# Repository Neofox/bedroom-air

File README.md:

# Bedroom Air

A bedroom CO₂ monitor you can build with an ESP32 and a Raspberry Pi Zero 2 W. Open Safari on your home Wi-Fi to see the room now, how high CO₂ climbed last night, and how much the temperature fell during a likely airing event.

## Build one

1. **Choose the parts.** Start with the 30-pin ESP32-WROOM-32, terminal-type Winsen MH-Z19C and DHT22 breakout. The BH1750 light sensor is optional. The parts list includes module variants, the Pi, power, and links to the carrier and case fasteners. [Parts list](docs/parts.md)
2. **Check the fit before ordering.** Print the A4 sheet at 100%, measure both 50 mm scale bars, and lay your actual modules on it. Then order the bare Rev A carrier and print the Rev C case. [Fit sheet](hardware/Board-fit-check.pdf) · [Gerbers and drills](hardware/Bedroom-Air-RevA-fabrication.zip) · [Printable parts](hardware/Case/)
3. **Solder and test.** Follow the connector map and staged power checks. The first USB flash can be done with the ESP32 lifted out of its sockets. [Carrier assembly](hardware/Assembly.md) · [Case assembly](hardware/Case/Assembly.md)
4. **Flash the ESP32 and enter your Wi-Fi settings over USB.** Once it joins your network, the live readings page is available at `http://bedroom-air.local/`. [Firmware setup and wireless updates](firmware/README.md)
5. **Set up the Pi for history and Apple Home.** The Pi saves one sample per minute on its microSD and serves the dashboard at `http://air-history.local:8080/`. After setup both devices can run on their own power supplies with the computer asleep. [Pi installation and pairing](pi/README.md)

The sensor and logging software ran on the breadboard prototype. The PCB and enclosure have electrical and digital fit checks. Physical fit and sensor behavior in a finished enclosure still need a first-build check.

## What you’ll see

**Live** refreshes roughly every three seconds. Select CO₂, temperature, humidity, or light to inspect its history. The ESP32 also keeps up to 24 hours of one-minute samples in RAM, which the Pi can collect after a Wi-Fi interruption while the ESP32 stays powered.

**Last night** shows the CO₂ peak, time above your chosen level, and how much of the night had valid data. **Airing out** looks for a sustained CO₂ drop and estimates the indoor temperature change and recovery time. Airing events are inferred from the sensors. The dashboard reports temperature change in °C. A heating bill would require energy-use and tariff data. [Example night report](docs/images/night-desktop.png) · [Phone dashboard](docs/images/live-phone.png)

**Apple Home** can show CO₂, temperature and humidity through the optional HomeKit service on the Pi. Light is available in the web dashboard. Each installation generates its own pairing code. The dashboard images in this repository use generated readings.

## Project files

| What you need | Where to find it |
| --- | --- |
| Arduino C++ sensor firmware, ESP32 web UI and bench sketches | [Firmware](firmware/) |
| Go logger, SQLite storage, Safari dashboard, reports and HomeKit service | [Pi source](pi/) |
| Ask Codex for current readings, recent trends, overnight CO₂ or inferred airing events | [Local MCP setup](mcp/) |
| PCB layout, schematic, local footprints and check reports | [Editable KiCad project](hardware/PCB/) · [Schematic PDF](hardware/PCB/Bedroom-Air-schematic.pdf) |
| Printable base, lid, sensor keeper, test gauge and parametric model | [Enclosure](hardware/Case/) |
| Design generation, rendering and fit checks | [Hardware design tools](hardware/tools/) |
| Prototype photos, wiring diagram and dashboard images | [Gallery](docs/gallery.md) |

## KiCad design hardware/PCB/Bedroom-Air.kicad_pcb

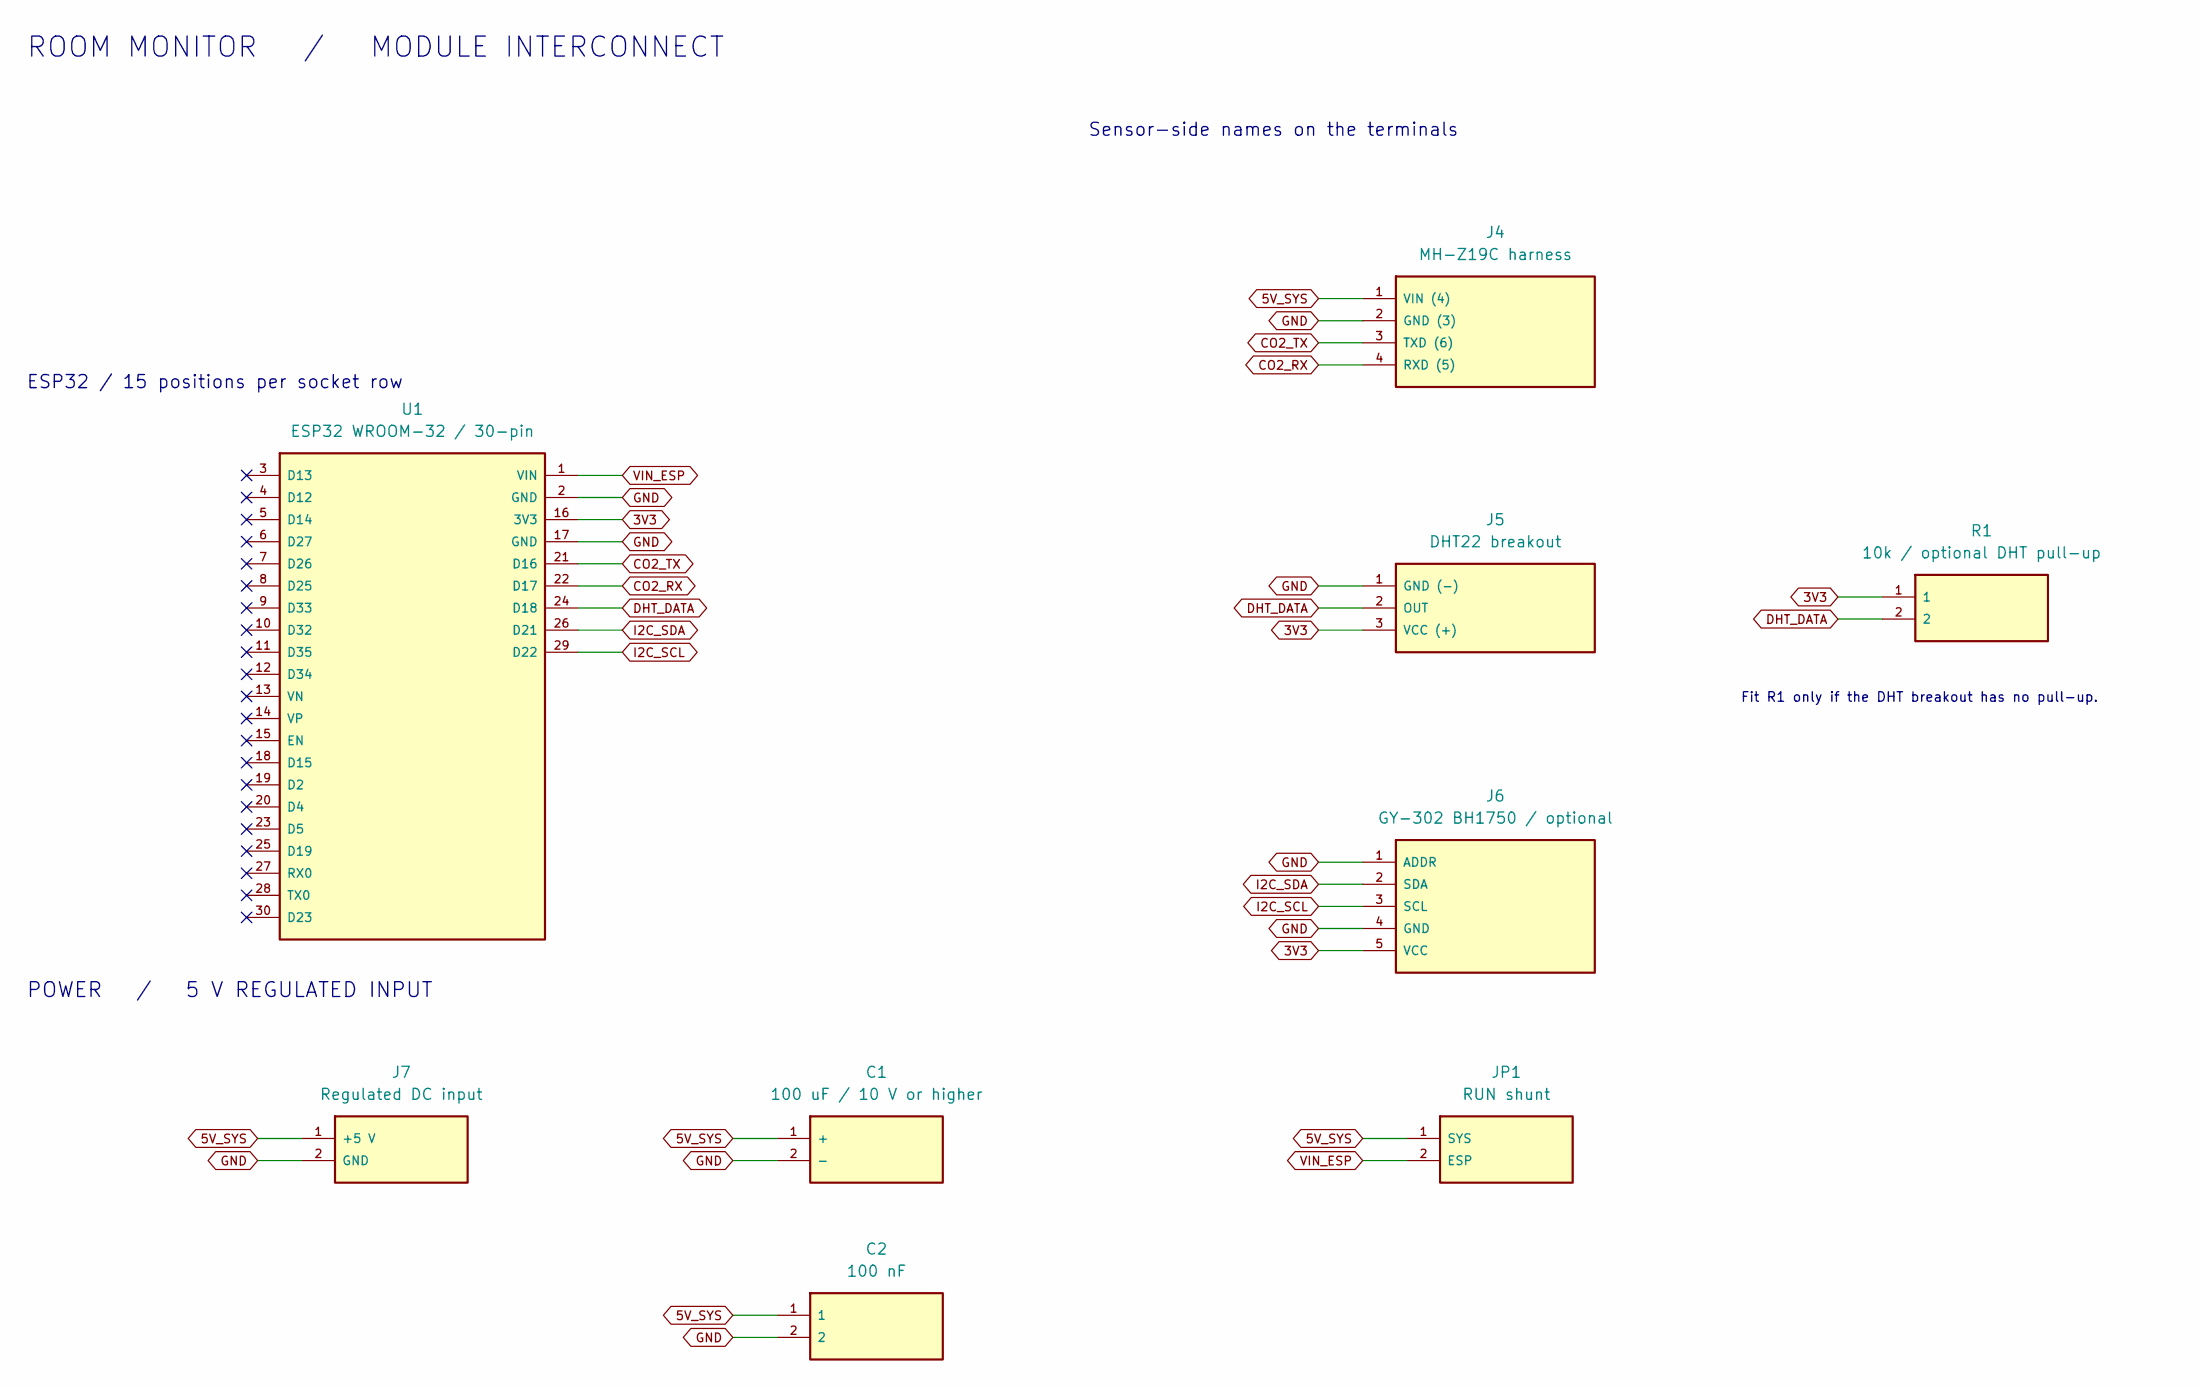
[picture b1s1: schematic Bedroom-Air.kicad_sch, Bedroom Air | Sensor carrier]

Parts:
C1: 100 uF / 10 V or higher; Cap_radial_D6.3_P2.5
C2: 100 nF; Cap_disc_P2.5
J4: MH-Z19C harness; Terminal_4P_5mm
J5: DHT22 breakout; Terminal_3P_5mm
J6: GY-302 BH1750 / optional; GY302_5P
J7: Regulated DC input; Terminal_2P_5mm
JP1: RUN shunt; Shunt_1x02
R1: 10k / optional DHT pull-up; Resistor_axial_P7.62
U1: ESP32 WROOM-32 / 30-pin; ESP32_30_DualWidth

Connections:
3V3: J5.3 (VCC (+)), J6.5 (VCC), R1.1, U1.16 (3V3)
5V_SYS: C1.1 (+), C2.1, J4.1 (VIN (4)), J7.1 (+5 V), JP1.1 (SYS)
CO2_RX: J4.4 (RXD (5)), U1.22 (D17)
CO2_TX: J4.3 (TXD (6)), U1.21 (D16)
DHT_DATA: J5.2 (OUT), R1.2, U1.24 (D18)
GND: C1.2 (-), C2.2, J4.2 (GND (3)), J5.1 (GND (-)), J6.1 (ADDR), J6.4 (GND), J7.2 (GND), U1.2 (GND), U1.17 (GND)
I2C_SCL: J6.3 (SCL), U1.29 (D22)
I2C_SDA: J6.2 (SDA), U1.26 (D21)
VIN_ESP: JP1.2 (ESP), U1.1 (VIN)

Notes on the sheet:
ROOM MONITOR / MODULE INTERCONNECT
ESP32 / 15 positions per socket row
Sensor-side names on the terminals
POWER / 5 V REGULATED INPUT
Fit R1 only if the DHT breakout has no pull-up.

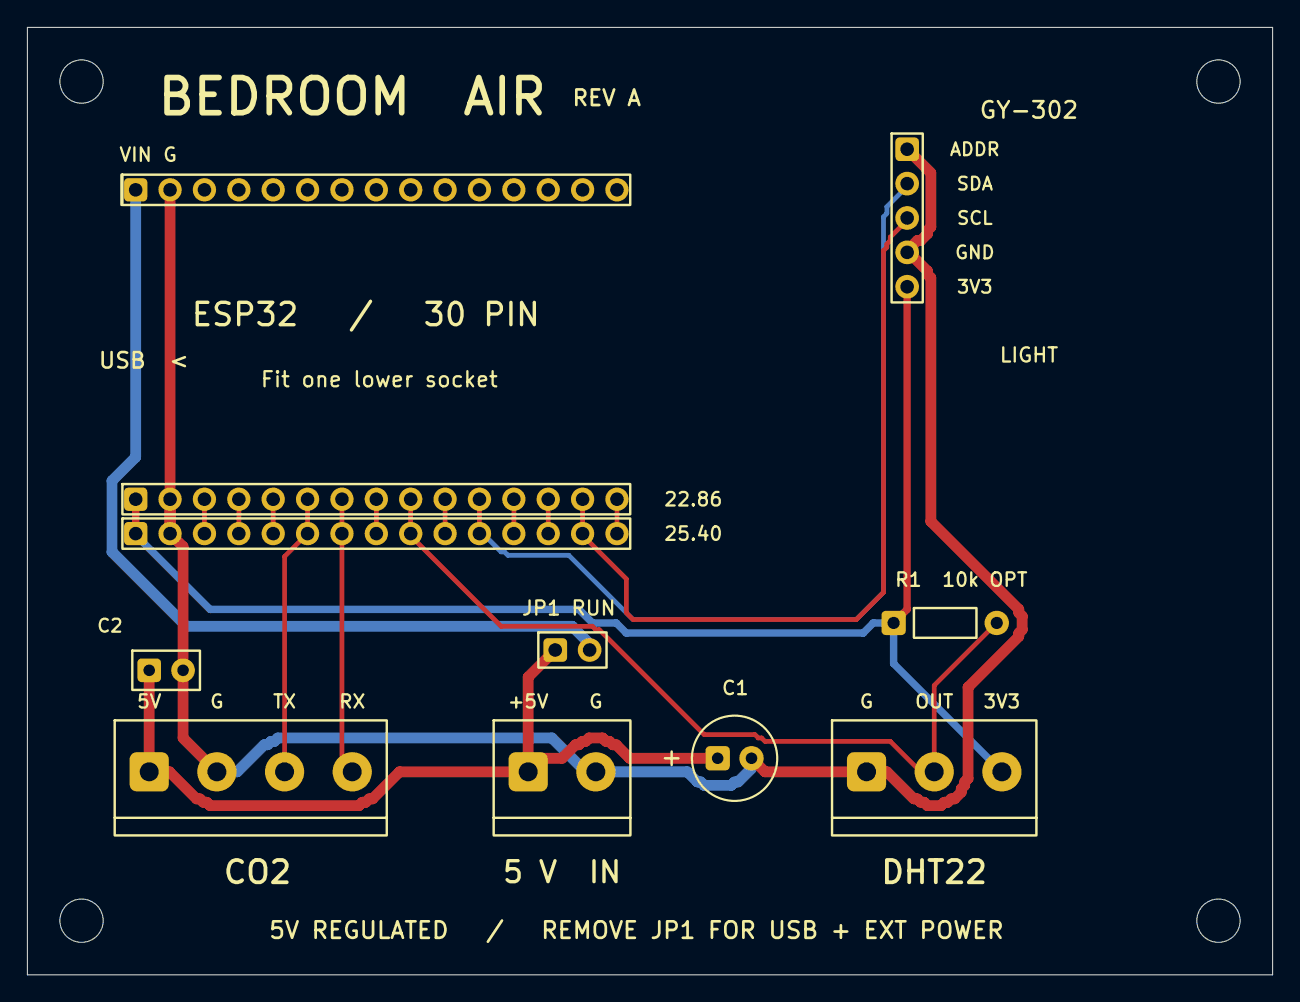
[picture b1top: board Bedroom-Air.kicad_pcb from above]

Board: 2 copper layers, 92.0 x 70.0 mm, 13 parts (0 on the bottom side), 9 nets.

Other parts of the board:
H1, H2, H3, H4: Mounting_M3
